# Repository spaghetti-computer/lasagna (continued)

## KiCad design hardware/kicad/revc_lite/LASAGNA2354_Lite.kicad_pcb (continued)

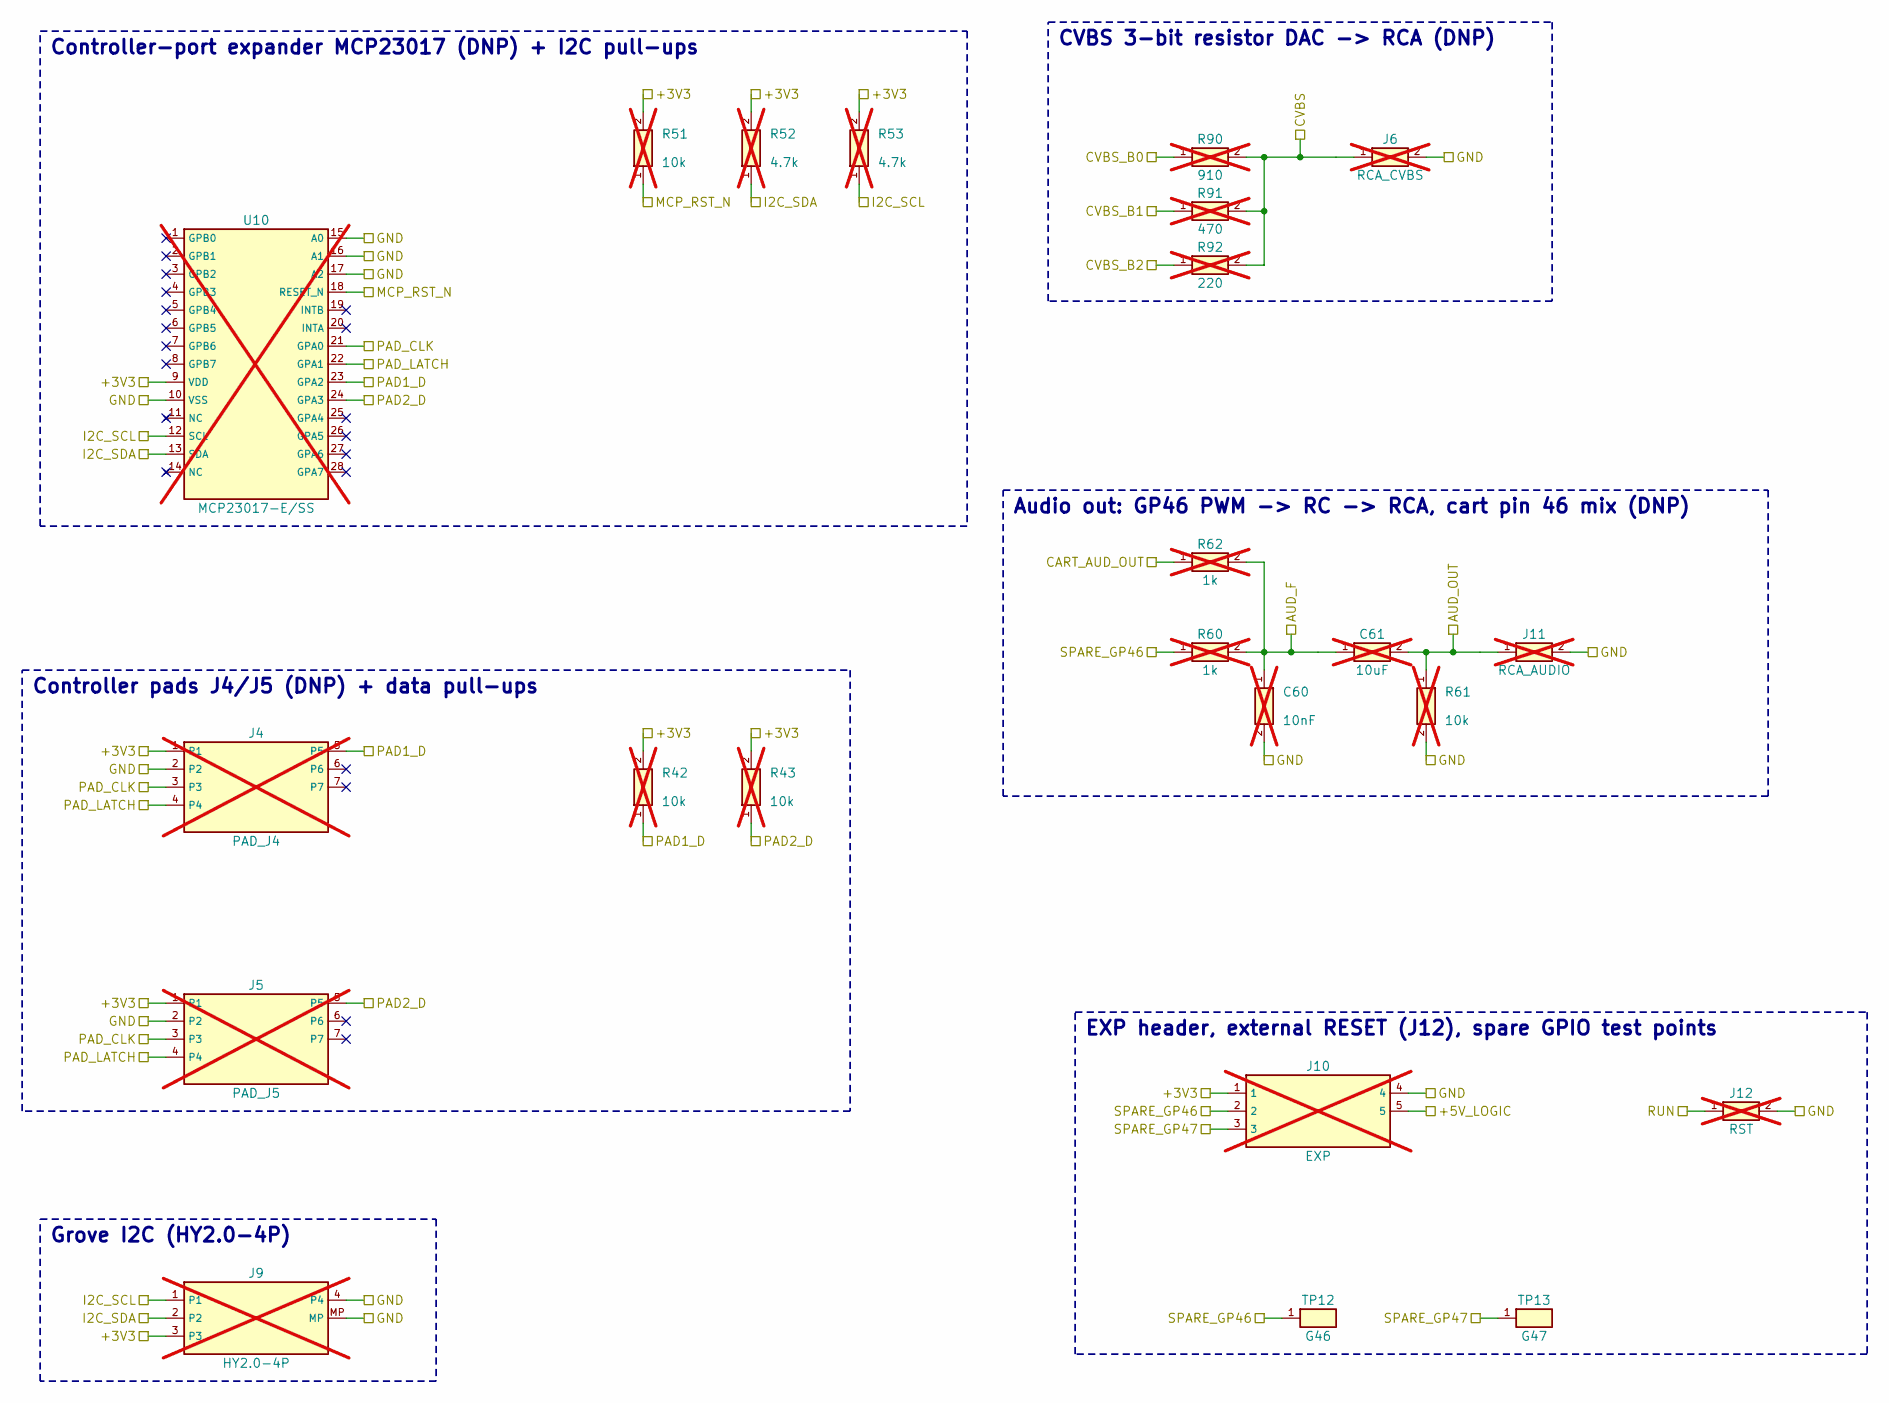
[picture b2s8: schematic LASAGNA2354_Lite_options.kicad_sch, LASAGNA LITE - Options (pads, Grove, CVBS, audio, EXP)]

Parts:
C60: 10nF; C_0603_1608Metric; MPN 10nF; LCSC C57112; not fitted
C61: 10uF; C_0805_2012Metric; MPN 10uF; LCSC C15850; not fitted
J4: PAD_J4; PinHeader_1x07_P2.54mm_Vertical; LCSC_Status hand-assembly / not PCBA; not fitted
J5: PAD_J5; PinHeader_1x07_P2.54mm_Vertical; LCSC_Status hand-assembly / not PCBA; not fitted
J6: RCA_CVBS; RCA_Avvicon_MJ-526; MPN MJ-526-Y; LCSC_Status hand-assembly / not PCBA; not fitted
J9: HY2.0-4P; JST_PH_S4B-PH-SM4-TB_1x04-1MP_P2.00mm_Horizontal; MPN HY2.0-4P-WT; LCSC C722729; not fitted
J10: EXP; PinHeader_1x05_P2.54mm_Vertical; LCSC_Status hand-assembly / not PCBA; not fitted
J11: RCA_AUDIO; RCA_Avvicon_MJ-526; MPN MJ-526-Y; LCSC_Status hand-assembly / not PCBA; not fitted
J12: RST; PinHeader_1x02_P2.54mm_Vertical; LCSC_Status hand-assembly / not PCBA; not fitted
R42, R43, R51, R61: 10k; R_0603_1608Metric; MPN 10k; LCSC C25804; not fitted
R52, R53: 4.7k; R_0603_1608Metric; MPN 4.7k; LCSC C23162; not fitted
R60, R62: 1k; R_0603_1608Metric; MPN 1k; LCSC C21190; not fitted
R90: 910; R_0603_1608Metric; MPN 910; LCSC C23264; not fitted
R91: 470; R_0603_1608Metric; MPN 470; LCSC C23179; not fitted
R92: 220; R_0603_1608Metric; MPN 220; LCSC C22962; not fitted
TP12: G46; TestPoint_THTPad_D2.0mm_Drill1.0mm; LCSC_Status no LCSC part
TP13: G47; TestPoint_THTPad_D2.0mm_Drill1.0mm; LCSC_Status no LCSC part
U10: MCP23017-E/SS; SSOP-28_5.3x10.2mm_P0.65mm; MPN MCP23017-E/SS; LCSC C506653; not fitted

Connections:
/+3V3: J4.1, J5.1, J9.3, J10.1, R42.2, R43.2, R51.2, R52.2, R53.2, U10.9 (VDD); also elsewhere on the board
/+5V_LOGIC: J10.5; also elsewhere on the board
/AUD_F: C60.1, C61.1, R60.2, R62.2
/AUD_OUT: C61.2, J11.1 (SIG), R61.1
/CART_AUD_OUT: R62.1; also elsewhere on the board
/CVBS: J6.1 (SIG), R90.2, R91.2, R92.2
/CVBS_B0: R90.1; also elsewhere on the board
/CVBS_B1: R91.1; also elsewhere on the board
/CVBS_B2: R92.1; also elsewhere on the board
/GND: C60.2, J4.2, J5.2, J6.2 (GND), J9.4, J9.MP, J10.4, J11.2 (GND), J12.2, R61.2, U10.10 (VSS), U10.15 (A0), U10.16 (A1), U10.17 (A2); also elsewhere on the board
/I2C_SCL: J9.1, R53.1, U10.12 (SCL); also elsewhere on the board
/I2C_SDA: J9.2, R52.1, U10.13 (SDA); also elsewhere on the board
/MCP_RST_N: R51.1, U10.18 (RESET_N)
/PAD1_D: J4.5, R42.1, U10.23 (GPA2)
/PAD2_D: J5.5, R43.1, U10.24 (GPA3)
/PAD_CLK: J4.3, J5.3, U10.21 (GPA0)
/PAD_LATCH: J4.4, J5.4, U10.22 (GPA1)
/RUN: J12.1; also elsewhere on the board
/SPARE_GP46: J10.2, R60.1, TP12.1; also elsewhere on the board
/SPARE_GP47: J10.3, TP13.1; also elsewhere on the board

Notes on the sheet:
Controller-port expander MCP23017 (DNP) + I2C pull-ups
Controller pads J4/J5 (DNP) + data pull-ups
Grove I2C (HY2.0-4P)
CVBS 3-bit resistor DAC -> RCA (DNP)
Audio out: GP46 PWM -> RC -> RCA, cart pin 46 mix (DNP)
EXP header, external RESET (J12), spare GPIO test points

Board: 2 copper layers, 78 parts (22 on the bottom side), 130 nets, no tracks yet.

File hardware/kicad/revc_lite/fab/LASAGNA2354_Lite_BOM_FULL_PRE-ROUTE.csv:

Qty,Value,Designator,Footprint,LCSC,MPN
1,WeAct RP2350B,U1,WeAct_RP2350B_CoreBoard,,WeAct RP2350B Core Board V1.0
1,Famicom_60pin_slot,J3,Hirose_CR22A-60D-2.54DS,,CR22A-60D-2.54DS(70)
2,SN74AHCT573PWR,"U2,U3",TSSOP-20_4.4x6.5mm_P0.65mm,C141311,SN74AHCT573PWR
2,74AHCT245PW,"U4,U5",TSSOP-20_4.4x6.5mm_P0.65mm,C173388,"74AHCT245PW,118"
2,74AHCT541PW,"U6,U7",TSSOP-20_4.4x6.5mm_P0.65mm,C84548,"74AHCT541PW,118"
1,SN74AHCT540PWR,U8,TSSOP-20_4.4x6.5mm_P0.65mm,C7626,SN74AHCT540PWR
4,10k,"R30,R31,R32,R39",R_0603_1608Metric,C25804,10k
4,10k (DNP),"R42,R43,R51,R61",R_0603_1608Metric,C25804,10k
1,PTC 0805 500mA,F1,Fuse_0805_2012Metric,C66452,SMD0805-050
1,10uF,C1,C_0805_2012Metric,C15850,10uF
1,910 (DNP),R90,R_0603_1608Metric,C23264,910
1,470 (DNP),R91,R_0603_1608Metric,C23179,470
1,220 (DNP),R92,R_0603_1608Metric,C22962,220
1,RCA_CVBS (DNP),J6,RCA_Avvicon_MJ-526,,MJ-526-Y
1,PAD_J4 (DNP),J4,PinHeader_1x07_P2.54mm_Vertical,,
1,PAD_J5 (DNP),J5,PinHeader_1x07_P2.54mm_Vertical,,
1,MCP23017-E/SS (DNP),U10,SSOP-28_5.3x10.2mm_P0.65mm,C506653,MCP23017-E/SS
2,4.7k (DNP),"R52,R53",R_0603_1608Metric,C23162,4.7k
1,HY2.0-4P (DNP),J9,JST_PH_S4B-PH-SM4-TB_1x04-1MP_P2.00mm_Horizontal,C722729,HY2.0-4P-WT
7,100nF,"C10,C11,C12,C13,C14,C15,C16",C_0603_1608Metric,C14663,100nF
1,100nF (DNP),C27,C_0603_1608Metric,C14663,100nF
1,SS34 (DNP),D2,D_SMA,C8678,SS34
1,CUT=USE D,JP1,SolderJumper-2_P1.3mm_Bridged_RoundedPad1.0x1.5mm,,
1,SHORT=BYPASS F,JP2,SolderJumper-2_P1.3mm_Open_RoundedPad1.0x1.5mm,,
1,EXP (DNP),J10,PinHeader_1x05_P2.54mm_Vertical,,
1,RST (DNP),J12,PinHeader_1x02_P2.54mm_Vertical,,
2,1k (DNP),"R60,R62",R_0603_1608Metric,C21190,1k
1,10nF (DNP),C60,C_0603_1608Metric,C57112,10nF
1,10uF (DNP),C61,C_0805_2012Metric,C15850,10uF
1,RCA_AUDIO (DNP),J11,RCA_Avvicon_MJ-526,,MJ-526-Y
4,33x4,"RN1,RN2,RN3,RN4",R_Array_Convex_4x0603,C25508,4D03WGJ0330T5E
1,5.1k,R41,R_0603_1608Metric,C23186,5.1k

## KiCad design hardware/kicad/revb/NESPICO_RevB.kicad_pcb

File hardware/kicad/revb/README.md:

# LASAGNA2354 (ラザニア2354) Rev.B KiCad project (PROPOSAL, NOT FAB-READY)

Status: schematic ERC 0 violations. PCB 100x100 mm, 2 layers, parts placed, **NOT ROUTED**
(499 unconnected items). Freerouting 2.1.0 left about 271 nets unrouted after 4 passes.
Do not order from fab/ yet. The gerber zip has "UNROUTED" in its name on purpose.

Regenerate with: python3 gen_sch.py; python3 gen_pcb.py; python3 export_fab.py
(design.py is the single source of truth)

## Unverified / open items
- Famicom 60-pin slot footprint: a 2x30 placeholder. Pitch and mechanics are not verified.
- DA-15 expansion pinout is not verified.
- RCA jack footprint is custom and not verified.
- $4016 parallel decode is not implemented. Only the SJ3 alternate input exists.
- CIRAM SRAM is omitted.
- Status buffer vs PPU latch contention is avoided by firmware only.
- 74HCT139 decode: possible glitch/race. Not analysed on hardware.
- LVC245 drives the cart with 3.3 V levels (assumed OK for NMOS/CMOS mask ROMs). Not verified.
- SN74AHCT574PWR (C129433) is a JLC Extended part. Stock was 0 when checked.
- Routing: needs a denser placement, or a 4-layer board, or manual routing.

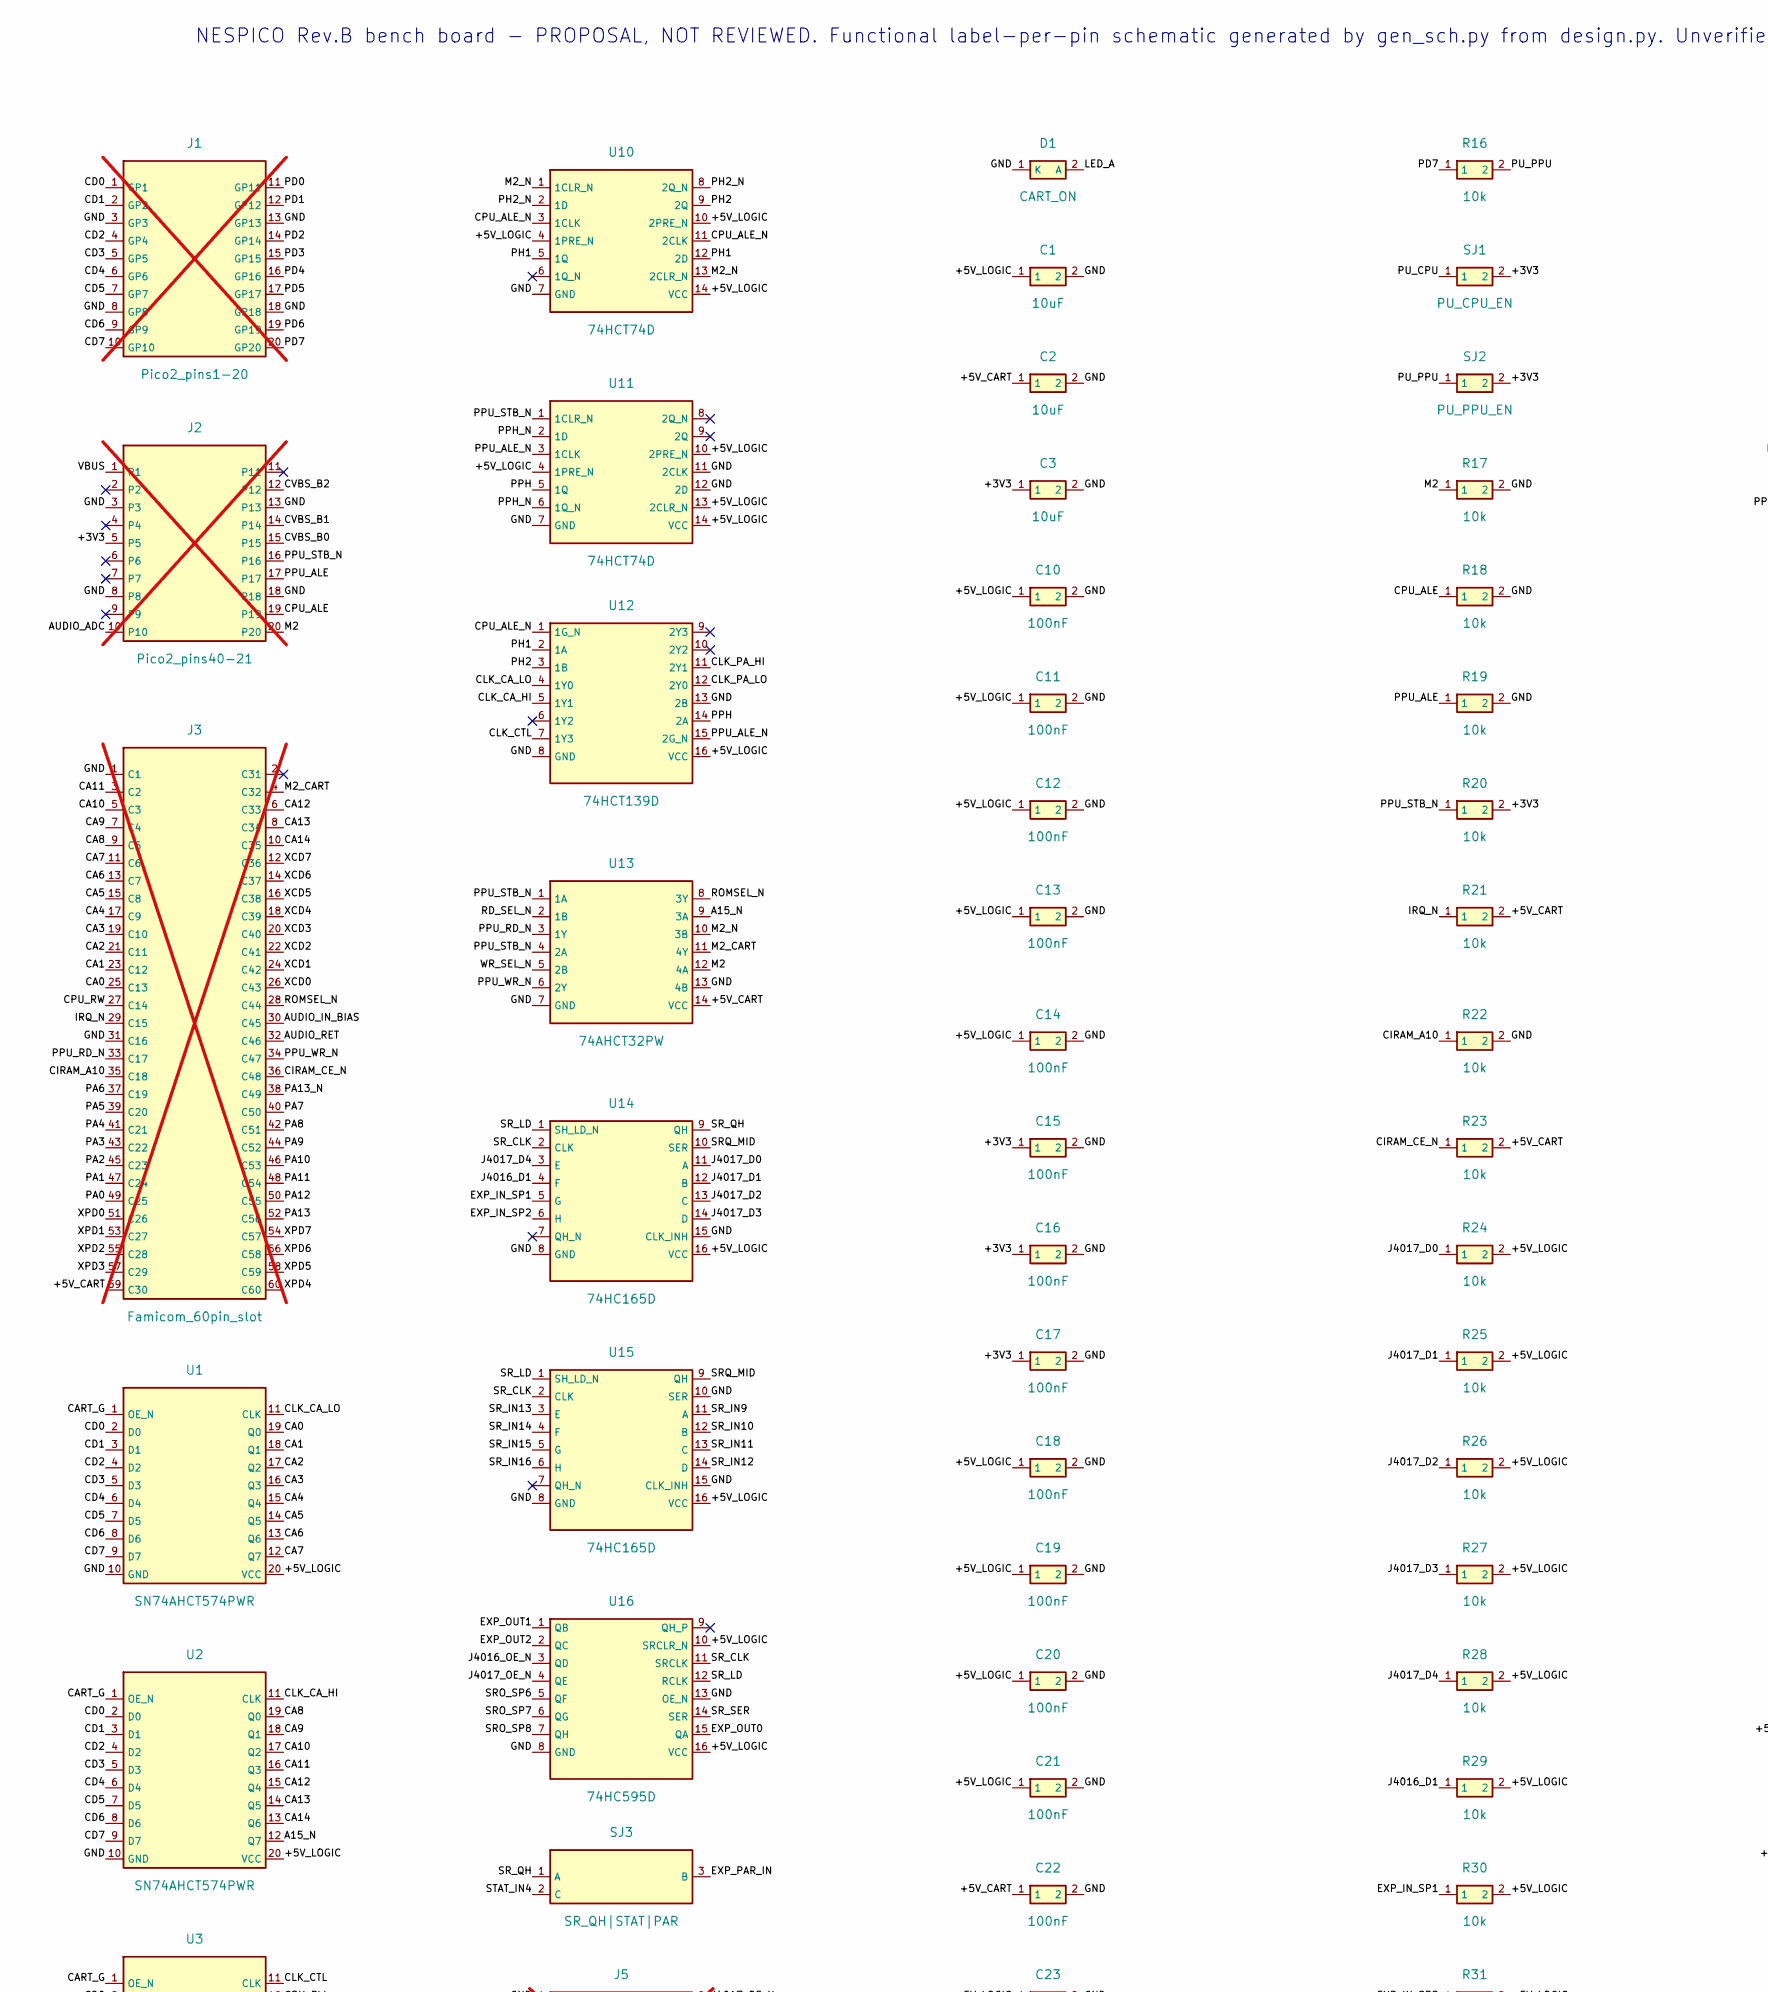
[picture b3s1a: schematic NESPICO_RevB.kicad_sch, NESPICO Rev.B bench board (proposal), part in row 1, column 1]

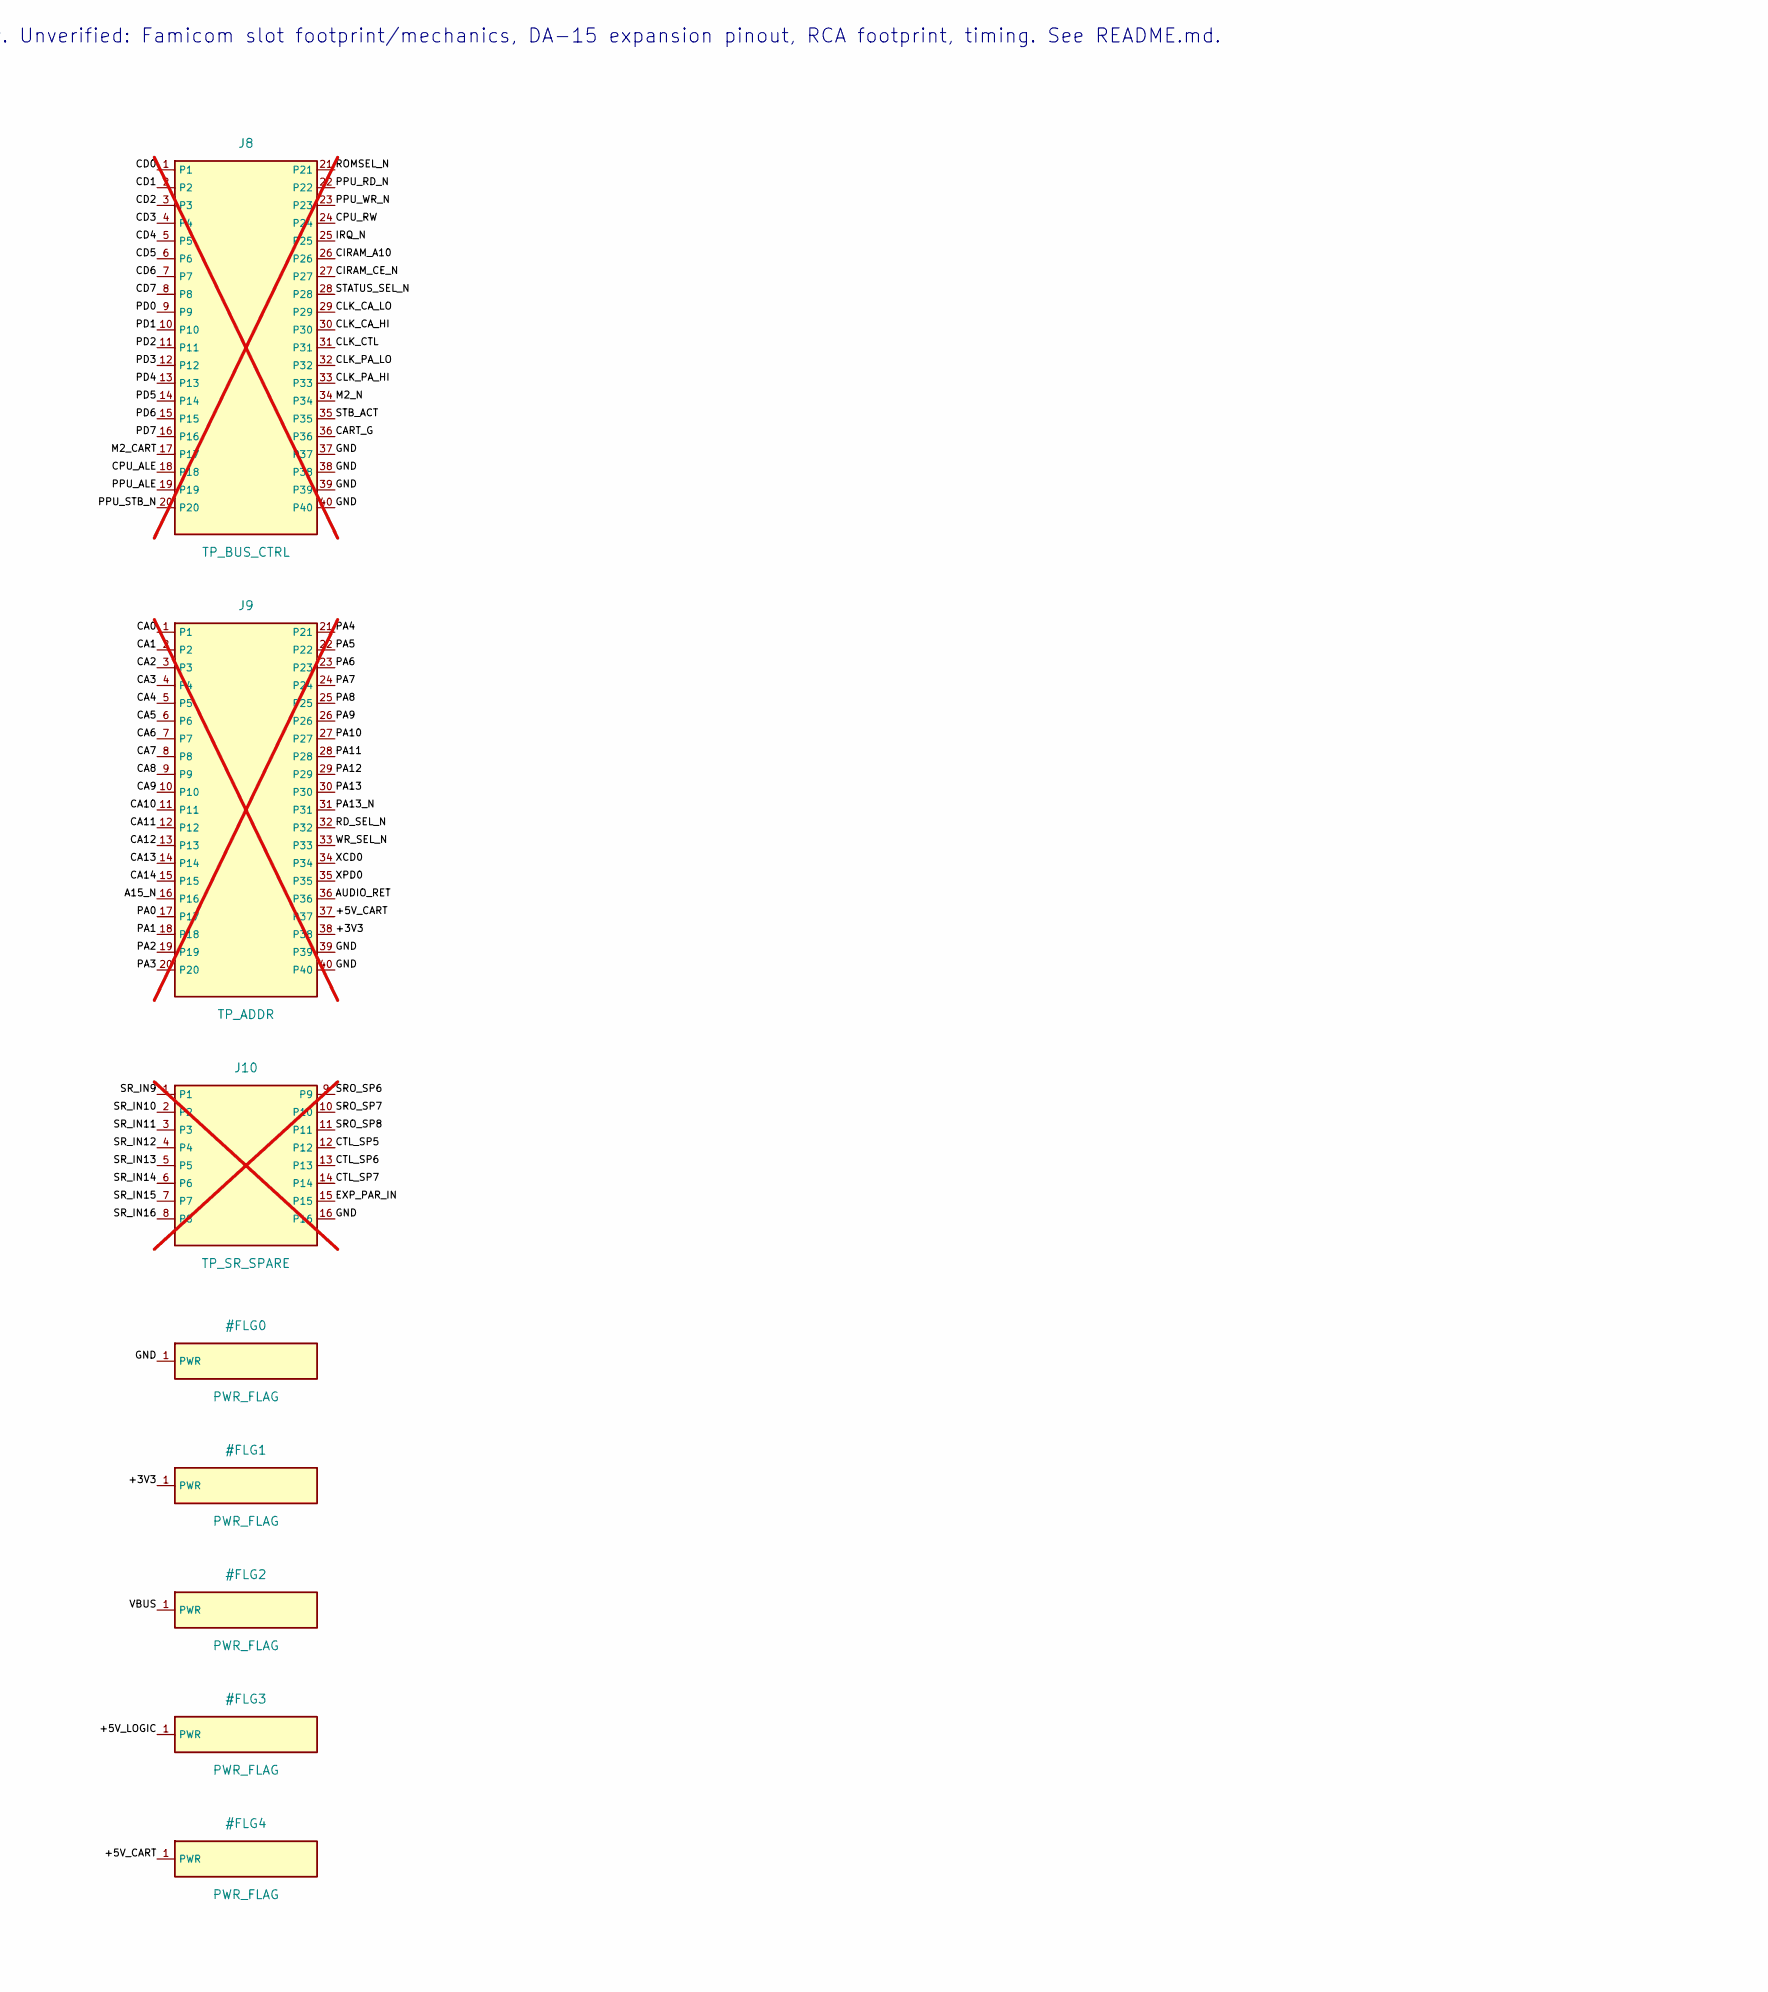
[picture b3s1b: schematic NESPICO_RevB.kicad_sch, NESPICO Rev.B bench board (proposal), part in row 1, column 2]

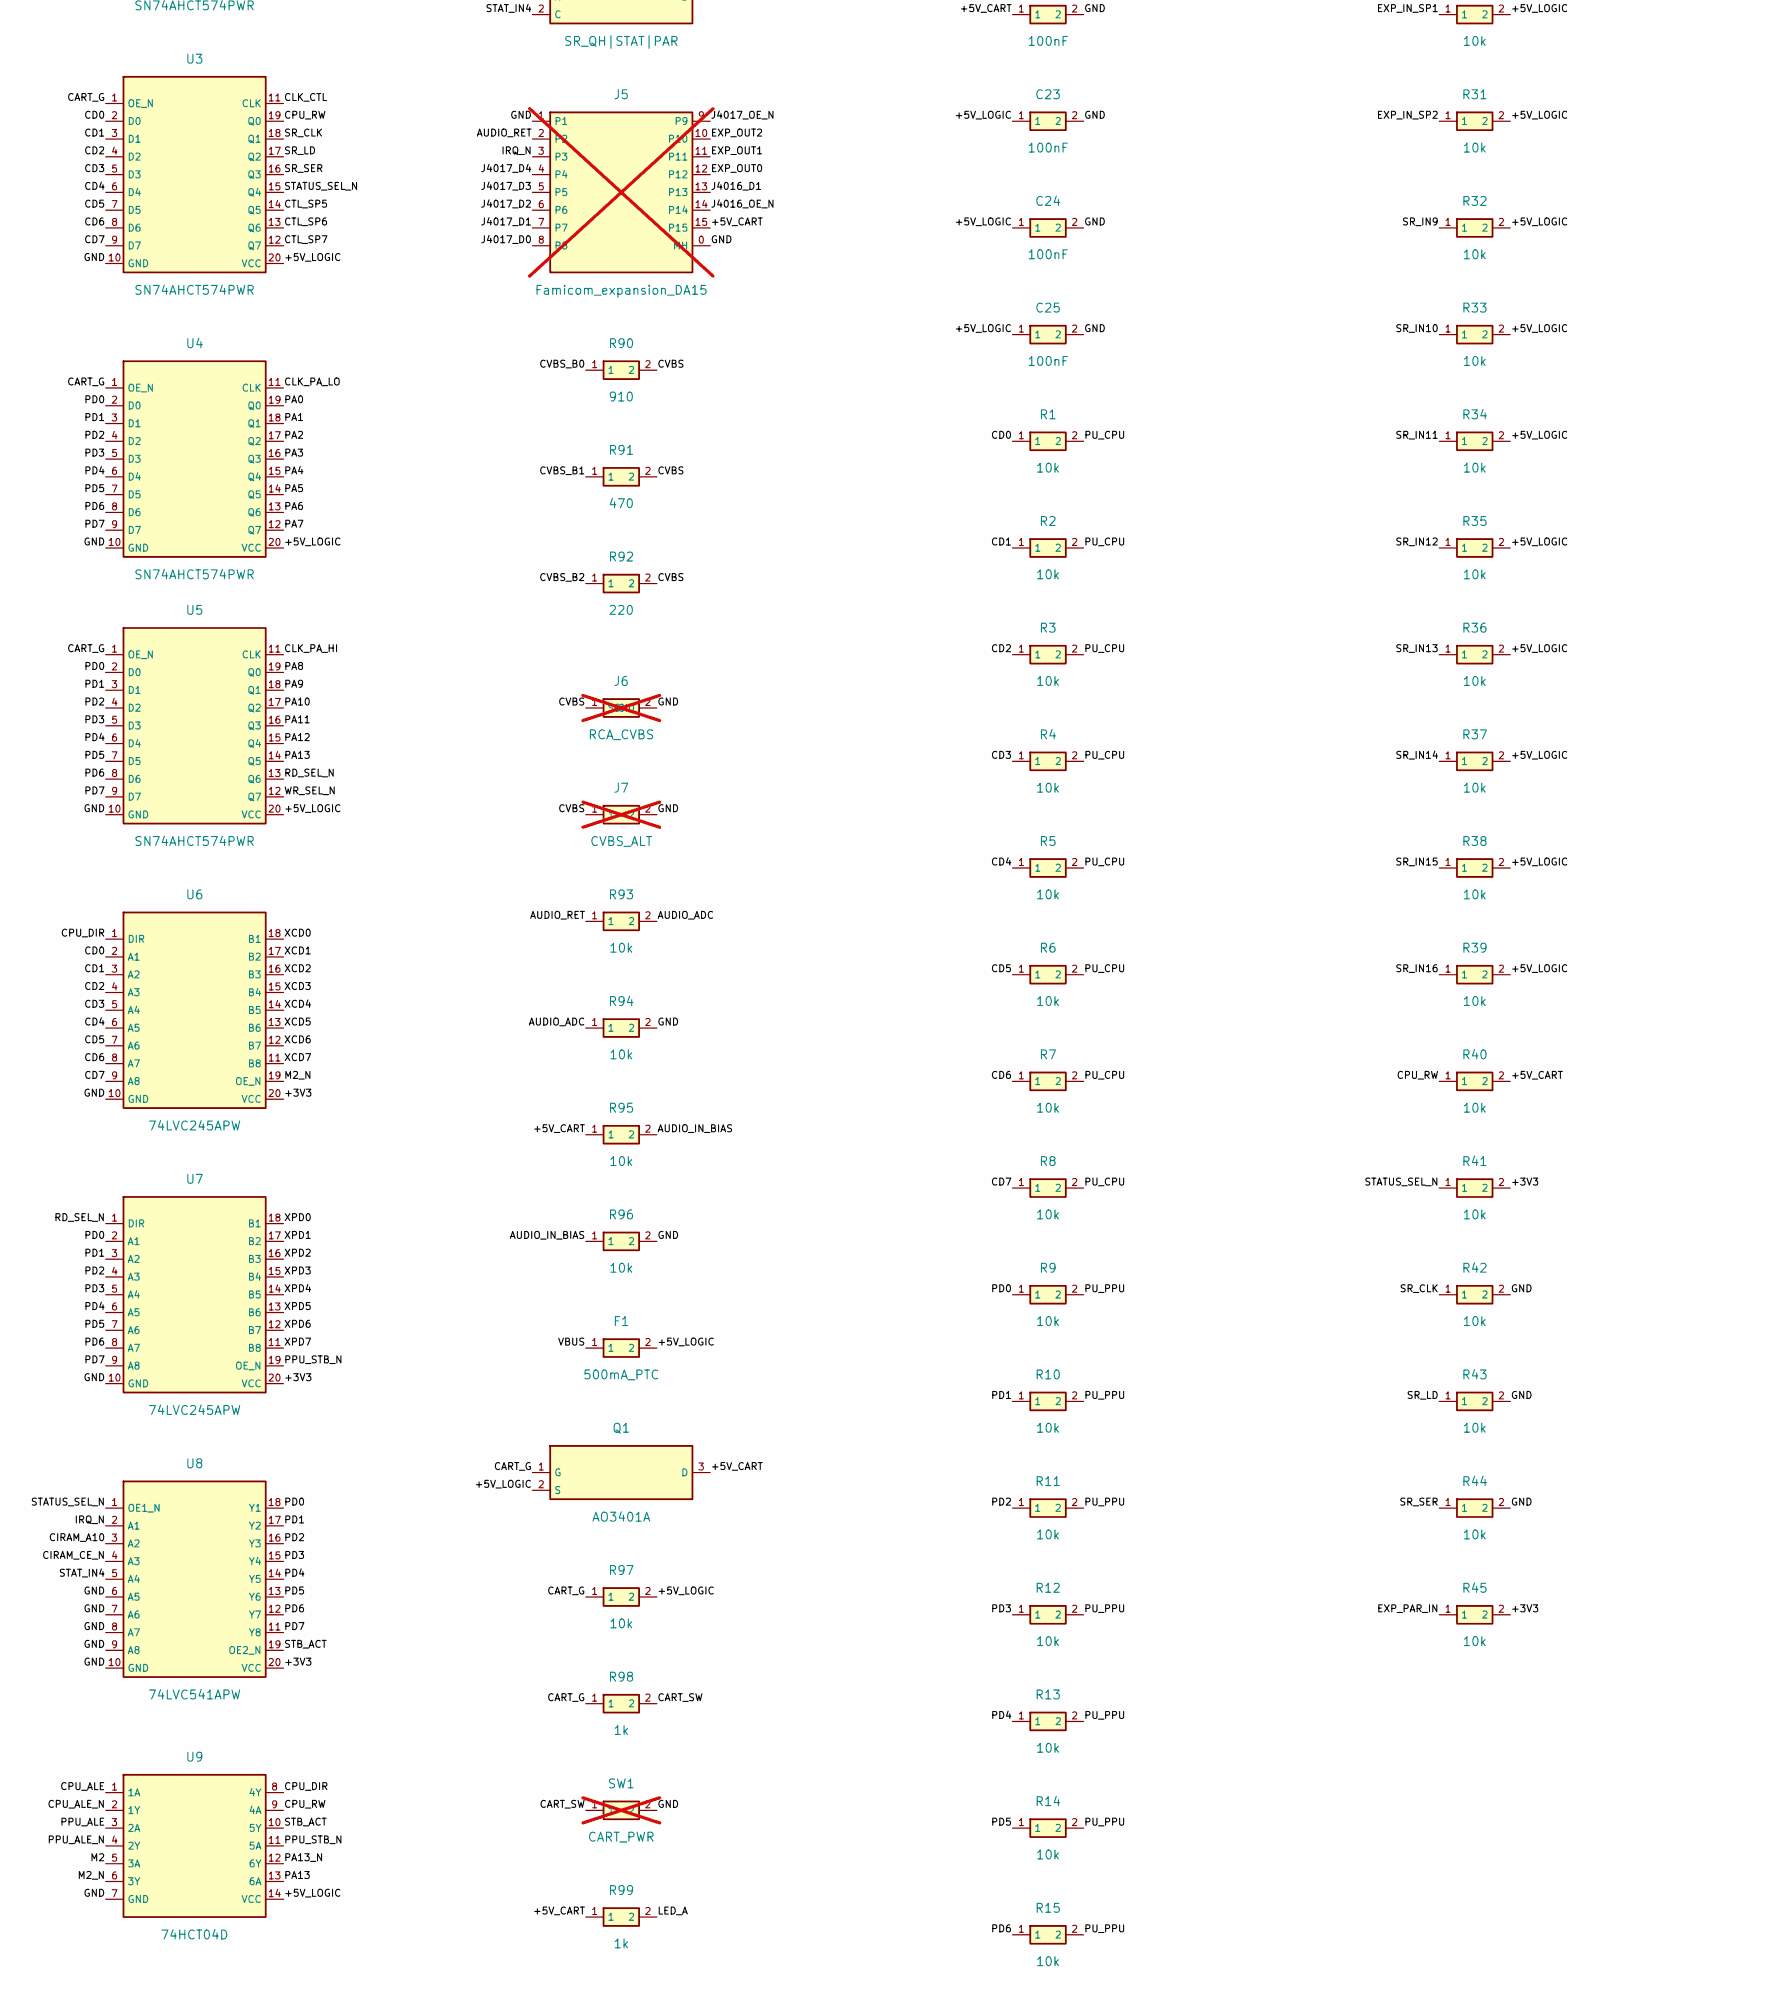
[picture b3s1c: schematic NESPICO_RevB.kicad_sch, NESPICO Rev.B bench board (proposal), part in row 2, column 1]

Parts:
C1, C2, C3: 10uF; C_0805_2012Metric; MPN 10uF; LCSC C15850
C10, C11, C12, C13, C14, C15, C16, C17, C18, C19, C20, C21, C22, C23, C24, C25: 100nF; C_0603_1608Metric; MPN 100nF; LCSC C14663
D1: CART_ON; LED_0603_1608Metric; MPN LED_G; LCSC C72043
F1: 500mA_PTC; Fuse_1206_3216Metric; MPN SMD1206-050-6; LCSC C46641012
J1: Pico2_pins1-20; PinSocket_1x20_P2.54mm_Vertical; LCSC_Status hand-assembly / not PCBA; not fitted
J2: Pico2_pins40-21; PinSocket_1x20_P2.54mm_Vertical; LCSC_Status hand-assembly / not PCBA; not fitted
J3: Famicom_60pin_slot; PinHeader_2x30_P2.54mm_Vertical; LCSC_Status hand-assembly / not PCBA; not fitted
J5: Famicom_expansion_DA15; DSUB-15_Socket_Horizontal_P2.77x2.84mm_EdgePinOffset9.40mm; LCSC_Status hand-assembly / not PCBA; not fitted
J6: RCA_CVBS; RCA_Jack_Generic_THT_UNVERIFIED; LCSC_Status hand-assembly / not PCBA; not fitted
J7: CVBS_ALT; PinHeader_1x02_P2.54mm_Vertical; LCSC_Status hand-assembly / not PCBA; not fitted
J8: TP_BUS_CTRL; PinHeader_2x20_P2.54mm_Vertical; LCSC_Status hand-assembly / not PCBA; not fitted
J9: TP_ADDR; PinHeader_2x20_P2.54mm_Vertical; LCSC_Status hand-assembly / not PCBA; not fitted
J10: TP_SR_SPARE; PinHeader_2x08_P2.54mm_Vertical; LCSC_Status hand-assembly / not PCBA; not fitted
Q1: AO3401A; SOT-23; MPN AO3401A; LCSC C15127
R1, R2, R3, R4, R5, R6, R7, R8, R9, R10, R11, R12, R13, R14, R15, R16, R17, R18, R19, R20, R21, R22, R23, R24, R25, R26, R27, R28, R29, R30, R31, R32, R33, R34, R35, R36, R37, R38, R39, R40, R41, R42, R43, R44, R45, R93, R94, R95, R96, R97: 10k; R_0603_1608Metric; MPN 10k; LCSC C25804
R90: 910; R_0603_1608Metric; MPN 910; LCSC C23264
R91: 470; R_0603_1608Metric; MPN 470; LCSC C23179
R92: 220; R_0603_1608Metric; MPN 220; LCSC C22962
R98, R99: 1k; R_0603_1608Metric; MPN 1k; LCSC C21190
SJ1: PU_CPU_EN; SolderJumper-2_P1.3mm_Bridged_Pad1.0x1.5mm; LCSC_Status no LCSC part
SJ2: PU_PPU_EN; SolderJumper-2_P1.3mm_Bridged_Pad1.0x1.5mm; LCSC_Status no LCSC part
SJ3: SR_QH|STAT|PAR; SolderJumper-3_P1.3mm_Bridged12_Pad1.0x1.5mm; LCSC_Status no LCSC part
SW1: CART_PWR; SW_DIP_SPSTx01_Slide_6.7x4.1mm_W7.62mm_P2.54mm_LowProfile; LCSC_Status hand-assembly / not PCBA; not fitted
U1, U2, U3, U4, U5: SN74AHCT574PWR; TSSOP-20_4.4x6.5mm_P0.65mm; MPN SN74AHCT574PWR; LCSC C129433
U6, U7: 74LVC245APW; TSSOP-20_4.4x6.5mm_P0.65mm; MPN 74LVC245APW,118; LCSC C6082
U8: 74LVC541APW; TSSOP-20_4.4x6.5mm_P0.65mm; MPN 74LVC541APW,118; LCSC C6093
U9: 74HCT04D; SOIC-14_3.9x8.7mm_P1.27mm; MPN 74HCT04D,653; LCSC C672096
U10, U11: 74HCT74D; SOIC-14_3.9x8.7mm_P1.27mm; MPN 74HCT74D,653; LCSC C686657
U12: 74HCT139D; SOIC-16_3.9x9.9mm_P1.27mm; MPN 74HCT139D,653; LCSC C545677
U13: 74AHCT32PW; TSSOP-14_4.4x5mm_P0.65mm; MPN 74AHCT32PW,118; LCSC C554656
U14, U15: 74HC165D; SOIC-16_3.9x9.9mm_P1.27mm; MPN 74HC165D,653; LCSC C5613
U16: 74HC595D; SOIC-16_3.9x9.9mm_P1.27mm; MPN 74HC595D,118; LCSC C5947

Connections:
+3V3: C3.1, C15.1, C16.1, C17.1, J2.5, J9.38, R20.2, R41.2, R45.2, SJ1.2, SJ2.2, U6.20 (VCC), U7.20 (VCC), U8.20 (VCC)
+5V_CART: C2.1, C22.1, J3.59 (C30), J5.15, J9.37, Q1.3 (D), R21.2, R23.2, R40.2, R95.1, R99.1, U13.14 (VCC)
+5V_LOGIC: C1.1, C10.1, C11.1, C12.1, C13.1, C14.1, C18.1, C19.1, C20.1, C21.1, C23.1, C24.1, C25.1, F1.2, Q1.2 (S), R24.2, R25.2, R26.2, R27.2, R28.2, R29.2, R30.2, R31.2, R32.2, R33.2, R34.2, R35.2, R36.2, R37.2, R38.2, R39.2, R97.2, U1.20 (VCC), U2.20 (VCC), U3.20 (VCC), U4.20 (VCC), U5.20 (VCC), U9.14 (VCC), U10.4 (1PRE_N), U10.10 (2PRE_N), U10.14 (VCC), U11.4 (1PRE_N), U11.10 (2PRE_N), U11.13 (2CLR_N), U11.14 (VCC), U12.16 (VCC), U14.16 (VCC), U15.16 (VCC), U16.10 (SRCLR_N), U16.16 (VCC)
A15_N: J9.16, U2.12 (Q7), U13.9 (3A)
AUDIO_ADC: J2.10, R93.2, R94.1
AUDIO_IN_BIAS: J3.30 (C45), R95.2, R96.1
AUDIO_RET: J3.32 (C46), J5.2, J9.36, R93.1
CA0: J3.25 (C13), J9.1, U1.19 (Q0)
CA1: J3.23 (C12), J9.2, U1.18 (Q1)
CA2: J3.21 (C11), J9.3, U1.17 (Q2)
CA3: J3.19 (C10), J9.4, U1.16 (Q3)
CA4: J3.17 (C9), J9.5, U1.15 (Q4)
CA5: J3.15 (C8), J9.6, U1.14 (Q5)
CA6: J3.13 (C7), J9.7, U1.13 (Q6)
CA7: J3.11 (C6), J9.8, U1.12 (Q7)
CA8: J3.9 (C5), J9.9, U2.19 (Q0)
CA9: J3.7 (C4), J9.10, U2.18 (Q1)
CA10: J3.5 (C3), J9.11, U2.17 (Q2)
CA11: J3.3 (C2), J9.12, U2.16 (Q3)
CA12: J3.6 (C33), J9.13, U2.15 (Q4)
CA13: J3.8 (C34), J9.14, U2.14 (Q5)
CA14: J3.10 (C35), J9.15, U2.13 (Q6)
CART_G: J8.36, Q1.1 (G), R97.1, R98.1, U1.1 (OE_N), U2.1 (OE_N), U3.1 (OE_N), U4.1 (OE_N), U5.1 (OE_N)
CART_SW: R98.2, SW1.1
CD0: J1.1 (GP1), J8.1, R1.1, U1.2 (D0), U2.2 (D0), U3.2 (D0), U6.2 (A1)
CD1: J1.2 (GP2), J8.2, R2.1, U1.3 (D1), U2.3 (D1), U3.3 (D1), U6.3 (A2)
CD2: J1.4 (GP4), J8.3, R3.1, U1.4 (D2), U2.4 (D2), U3.4 (D2), U6.4 (A3)
CD3: J1.5 (GP5), J8.4, R4.1, U1.5 (D3), U2.5 (D3), U3.5 (D3), U6.5 (A4)
CD4: J1.6 (GP6), J8.5, R5.1, U1.6 (D4), U2.6 (D4), U3.6 (D4), U6.6 (A5)
CD5: J1.7 (GP7), J8.6, R6.1, U1.7 (D5), U2.7 (D5), U3.7 (D5), U6.7 (A6)
CD6: J1.9 (GP9), J8.7, R7.1, U1.8 (D6), U2.8 (D6), U3.8 (D6), U6.8 (A7)
CD7: J1.10 (GP10), J8.8, R8.1, U1.9 (D7), U2.9 (D7), U3.9 (D7), U6.9 (A8)
CIRAM_A10: J3.35 (C18), J8.26, R22.1, U8.3 (A2)
CIRAM_CE_N: J3.36 (C48), J8.27, R23.1, U8.4 (A3)
CLK_CA_HI: J8.30, U2.11 (CLK), U12.5 (1Y1)
CLK_CA_LO: J8.29, U1.11 (CLK), U12.4 (1Y0)
CLK_CTL: J8.31, U3.11 (CLK), U12.7 (1Y3)
CLK_PA_HI: J8.33, U5.11 (CLK), U12.11 (2Y1)
CLK_PA_LO: J8.32, U4.11 (CLK), U12.12 (2Y0)
CPU_ALE: J2.19, J8.18, R18.1, U9.1 (1A)
CPU_ALE_N: U9.2 (1Y), U10.3 (1CLK), U10.11 (2CLK), U12.1 (1G_N)
CPU_DIR: U6.1 (DIR), U9.8 (4Y)
CPU_RW: J3.27 (C14), J8.24, R40.1, U3.19 (Q0), U9.9 (4A)
CTL_SP5: J10.12, U3.14 (Q5)
CTL_SP6: J10.13, U3.13 (Q6)
CTL_SP7: J10.14, U3.12 (Q7)
CVBS: J6.1 (SIG), J7.1, R90.2, R91.2, R92.2
CVBS_B0: J2.15, R90.1
CVBS_B1: J2.14, R91.1
CVBS_B2: J2.12, R92.1
EXP_IN_SP1: R30.1, U14.5 (G)
EXP_IN_SP2: R31.1, U14.6 (H)
EXP_OUT0: J5.12, U16.15 (QA)
EXP_OUT1: J5.11, U16.1 (QB)
EXP_OUT2: J5.10, U16.2 (QC)
EXP_PAR_IN: J10.15, R45.1, SJ3.3 (B)
GND: C1.2, C2.2, C3.2, C10.2, C11.2, C12.2, C13.2, C14.2, C15.2, C16.2, C17.2, C18.2, C19.2, C20.2, C21.2, C22.2, C23.2, C24.2, C25.2, D1.1 (K), J1.3 (GP3), J1.8 (GP8), J1.13 (GP13), J1.18 (GP18), J2.3, J2.8, J2.13, J2.18, J3.1 (C1), J3.31 (C16), J5.0 (MH), J5.1, J6.2 (GND), J7.2, J8.37, J8.38, J8.39, J8.40, J9.39, J9.40, J10.16, R17.2, R18.2, R19.2, R22.2, R42.2, R43.2, R44.2, R94.2, R96.2, SW1.2, U1.10 (GND), U2.10 (GND), U3.10 (GND), U4.10 (GND), U5.10 (GND), U6.10 (GND), U7.10 (GND), U8.6 (A5), U8.7 (A6), U8.8 (A7), U8.9 (A8), U8.10 (GND), U9.7 (GND), U10.7 (GND), U11.7 (GND), U11.11 (2CLK), U11.12 (2D), U12.8 (GND), U12.13 (2B), U13.7 (GND), U13.13 (4B), U14.8 (GND), U14.15 (CLK_INH), U15.8 (GND), U15.10 (SER), U15.15 (CLK_INH), U16.8 (GND), U16.13 (OE_N)
IRQ_N: J3.29 (C15), J5.3, J8.25, R21.1, U8.2 (A1)
J4016_D1: J5.13, R29.1, U14.4 (F)
J4016_OE_N: J5.14, U16.3 (QD)
J4017_D0: J5.8, R24.1, U14.11 (A)
J4017_D1: J5.7, R25.1, U14.12 (B)
J4017_D2: J5.6, R26.1, U14.13 (C)
J4017_D3: J5.5, R27.1, U14.14 (D)
J4017_D4: J5.4, R28.1, U14.3 (E)
J4017_OE_N: J5.9, U16.4 (QE)
LED_A: D1.2 (A), R99.2
M2: J2.20, R17.1, U9.5 (3A), U13.12 (4A)
M2_CART: J3.4 (C32), J8.17, U13.11 (4Y)
M2_N: J8.34, U6.19 (OE_N), U9.6 (3Y), U10.1 (1CLR_N), U10.13 (2CLR_N), U13.10 (3B)
PA0: J3.49 (C25), J9.17, U4.19 (Q0)
PA1: J3.47 (C24), J9.18, U4.18 (Q1)
PA2: J3.45 (C23), J9.19, U4.17 (Q2)
PA3: J3.43 (C22), J9.20, U4.16 (Q3)
PA4: J3.41 (C21), J9.21, U4.15 (Q4)
PA5: J3.39 (C20), J9.22, U4.14 (Q5)
PA6: J3.37 (C19), J9.23, U4.13 (Q6)
PA7: J3.40 (C50), J9.24, U4.12 (Q7)
PA8: J3.42 (C51), J9.25, U5.19 (Q0)
PA9: J3.44 (C52), J9.26, U5.18 (Q1)
PA10: J3.46 (C53), J9.27, U5.17 (Q2)
PA11: J3.48 (C54), J9.28, U5.16 (Q3)
PA12: J3.50 (C55), J9.29, U5.15 (Q4)
PA13: J3.52 (C56), J9.30, U5.14 (Q5), U9.13 (6A)
PA13_N: J3.38 (C49), J9.31, U9.12 (6Y)
PD0: J1.11 (GP11), J8.9, R9.1, U4.2 (D0), U5.2 (D0), U7.2 (A1), U8.18 (Y1)
PD1: J1.12 (GP12), J8.10, R10.1, U4.3 (D1), U5.3 (D1), U7.3 (A2), U8.17 (Y2)
PD2: J1.14 (GP14), J8.11, R11.1, U4.4 (D2), U5.4 (D2), U7.4 (A3), U8.16 (Y3)
PD3: J1.15 (GP15), J8.12, R12.1, U4.5 (D3), U5.5 (D3), U7.5 (A4), U8.15 (Y4)
PD4: J1.16 (GP16), J8.13, R13.1, U4.6 (D4), U5.6 (D4), U7.6 (A5), U8.14 (Y5)
PD5: J1.17 (GP17), J8.14, R14.1, U4.7 (D5), U5.7 (D5), U7.7 (A6), U8.13 (Y6)
PD6: J1.19 (GP19), J8.15, R15.1, U4.8 (D6), U5.8 (D6), U7.8 (A7), U8.12 (Y7)
PD7: J1.20 (GP20), J8.16, R16.1, U4.9 (D7), U5.9 (D7), U7.9 (A8), U8.11 (Y8)
PH1: U10.5 (1Q), U10.12 (2D), U12.2 (1A)
PH2: U10.9 (2Q), U12.3 (1B)
PH2_N: U10.2 (1D), U10.8 (2Q_N)
PPH: U11.5 (1Q), U12.14 (2A)
PPH_N: U11.2 (1D), U11.6 (1Q_N)
PPU_ALE: J2.17, J8.19, R19.1, U9.3 (2A)
PPU_ALE_N: U9.4 (2Y), U11.3 (1CLK), U12.15 (2G_N)
PPU_RD_N: J3.33 (C17), J8.22, U13.3 (1Y)
PPU_STB_N: J2.16, J8.20, R20.1, U7.19 (OE_N), U9.11 (5A), U11.1 (1CLR_N), U13.1 (1A), U13.4 (2A)
PPU_WR_N: J3.34 (C47), J8.23, U13.6 (2Y)
PU_CPU: R1.2, R2.2, R3.2, R4.2, R5.2, R6.2, R7.2, R8.2, SJ1.1
PU_PPU: R9.2, R10.2, R11.2, R12.2, R13.2, R14.2, R15.2, R16.2, SJ2.1
RD_SEL_N: J9.32, U5.13 (Q6), U7.1 (DIR), U13.2 (1B)
ROMSEL_N: J3.28 (C44), J8.21, U13.8 (3Y)
SRO_SP6: J10.9, U16.5 (QF)
SRO_SP7: J10.10, U16.6 (QG)
SRO_SP8: J10.11, U16.7 (QH)
SRQ_MID: U14.10 (SER), U15.9 (QH)
SR_CLK: R42.1, U3.18 (Q1), U14.2 (CLK), U15.2 (CLK), U16.11 (SRCLK)
SR_IN9: J10.1, R32.1, U15.11 (A)
SR_IN10: J10.2, R33.1, U15.12 (B)
SR_IN11: J10.3, R34.1, U15.13 (C)
SR_IN12: J10.4, R35.1, U15.14 (D)
SR_IN13: J10.5, R36.1, U15.3 (E)
SR_IN14: J10.6, R37.1, U15.4 (F)
SR_IN15: J10.7, R38.1, U15.5 (G)
SR_IN16: J10.8, R39.1, U15.6 (H)
SR_LD: R43.1, U3.17 (Q2), U14.1 (SH_LD_N), U15.1 (SH_LD_N), U16.12 (RCLK)
SR_QH: SJ3.1 (A), U14.9 (QH)
SR_SER: R44.1, U3.16 (Q3), U16.14 (SER)
STATUS_SEL_N: J8.28, R41.1, U3.15 (Q4), U8.1 (OE1_N)
STAT_IN4: SJ3.2 (C), U8.5 (A4)
STB_ACT: J8.35, U8.19 (OE2_N), U9.10 (5Y)
VBUS: F1.1, J2.1
WR_SEL_N: J9.33, U5.12 (Q7), U13.5 (2B)
XCD0: J3.26 (C43), J9.34, U6.18 (B1)
XCD1: J3.24 (C42), U6.17 (B2)
XCD2: J3.22 (C41), U6.16 (B3)
XCD3: J3.20 (C40), U6.15 (B4)
XCD4: J3.18 (C39), U6.14 (B5)
XCD5: J3.16 (C38), U6.13 (B6)
XCD6: J3.14 (C37), U6.12 (B7)
XCD7: J3.12 (C36), U6.11 (B8)
XPD0: J3.51 (C26), J9.35, U7.18 (B1)
XPD1: J3.53 (C27), U7.17 (B2)
XPD2: J3.55 (C28), U7.16 (B3)
XPD3: J3.57 (C29), U7.15 (B4)
XPD4: J3.60 (C60), U7.14 (B5)
XPD5: J3.58 (C59), U7.13 (B6)
XPD6: J3.56 (C58), U7.12 (B7)
XPD7: J3.54 (C57), U7.11 (B8)

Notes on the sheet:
NESPICO Rev.B bench board - PROPOSAL, NOT REVIEWED. Functional label-per-pin schematic generated by gen_sch.py from design.py. Unverified: Famicom slot footprint/mechanics, DA-15 expansion pinout, RCA footprint, timing. See README.md.
